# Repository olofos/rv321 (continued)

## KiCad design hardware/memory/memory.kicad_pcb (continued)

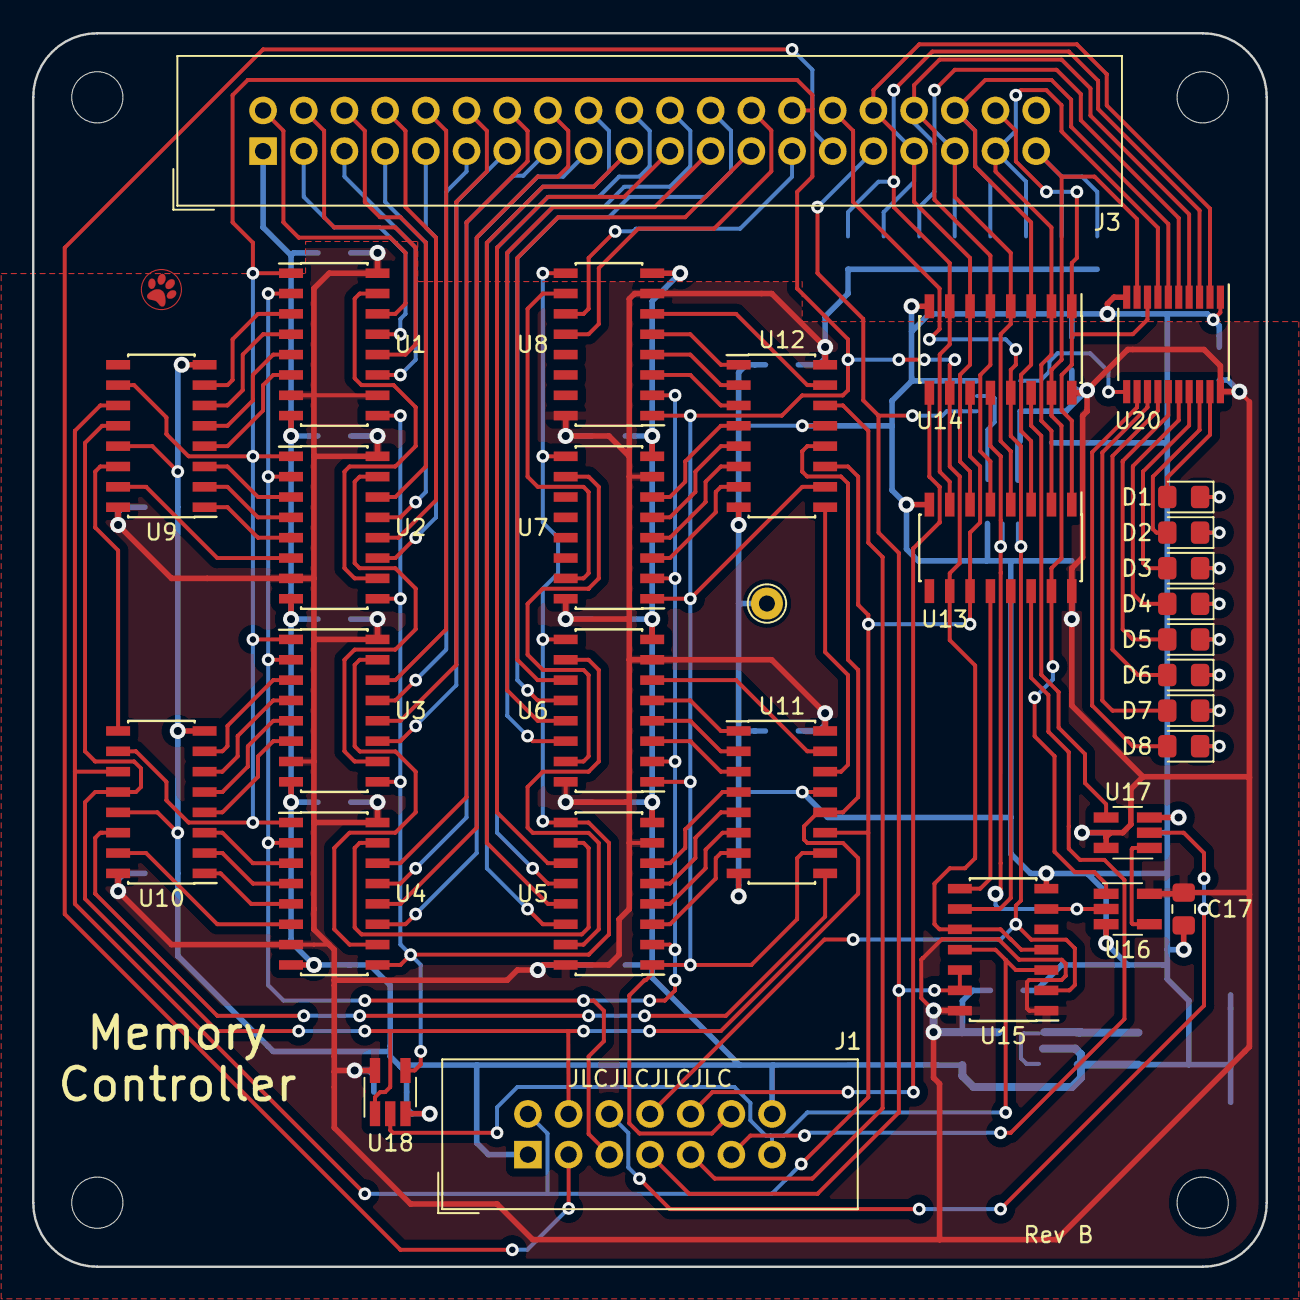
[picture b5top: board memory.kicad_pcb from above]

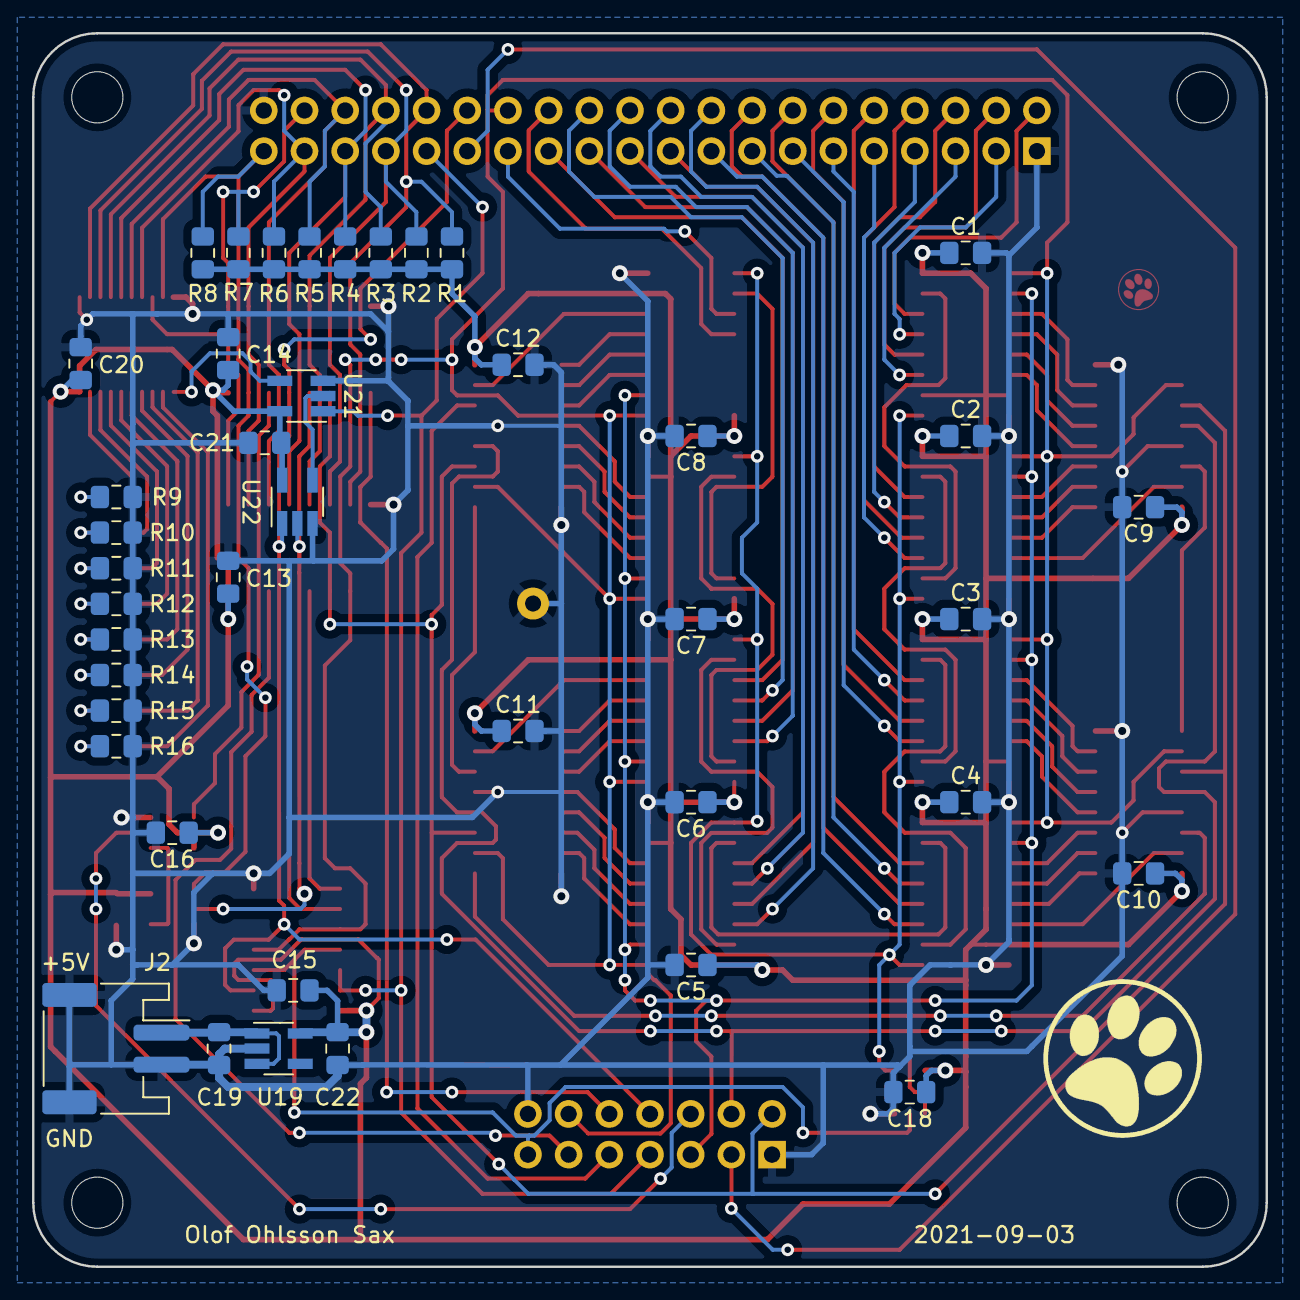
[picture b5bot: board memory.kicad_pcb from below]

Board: 2 copper layers, 77.0 x 77.0 mm, 76 parts (41 on the bottom side), 115 nets.

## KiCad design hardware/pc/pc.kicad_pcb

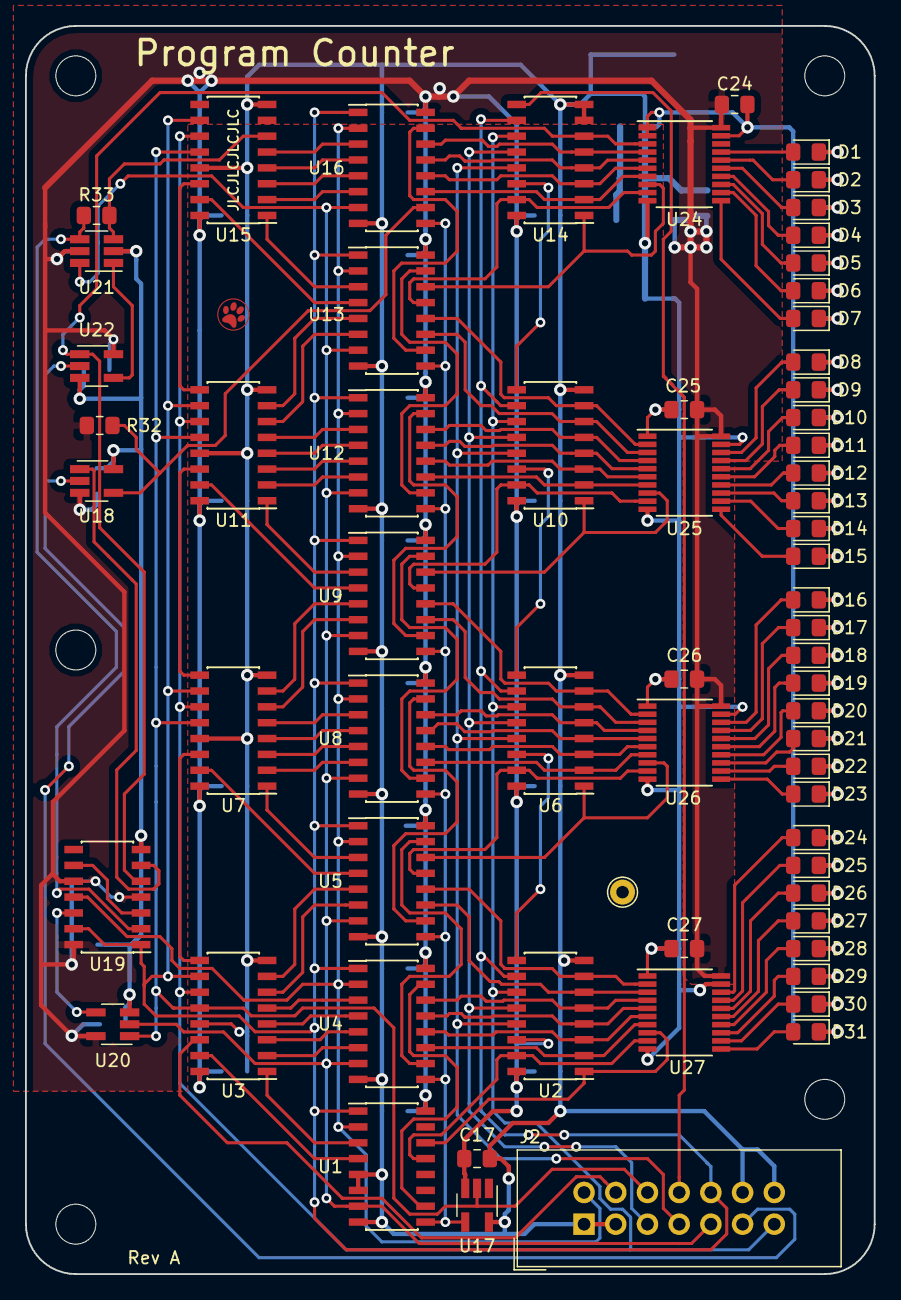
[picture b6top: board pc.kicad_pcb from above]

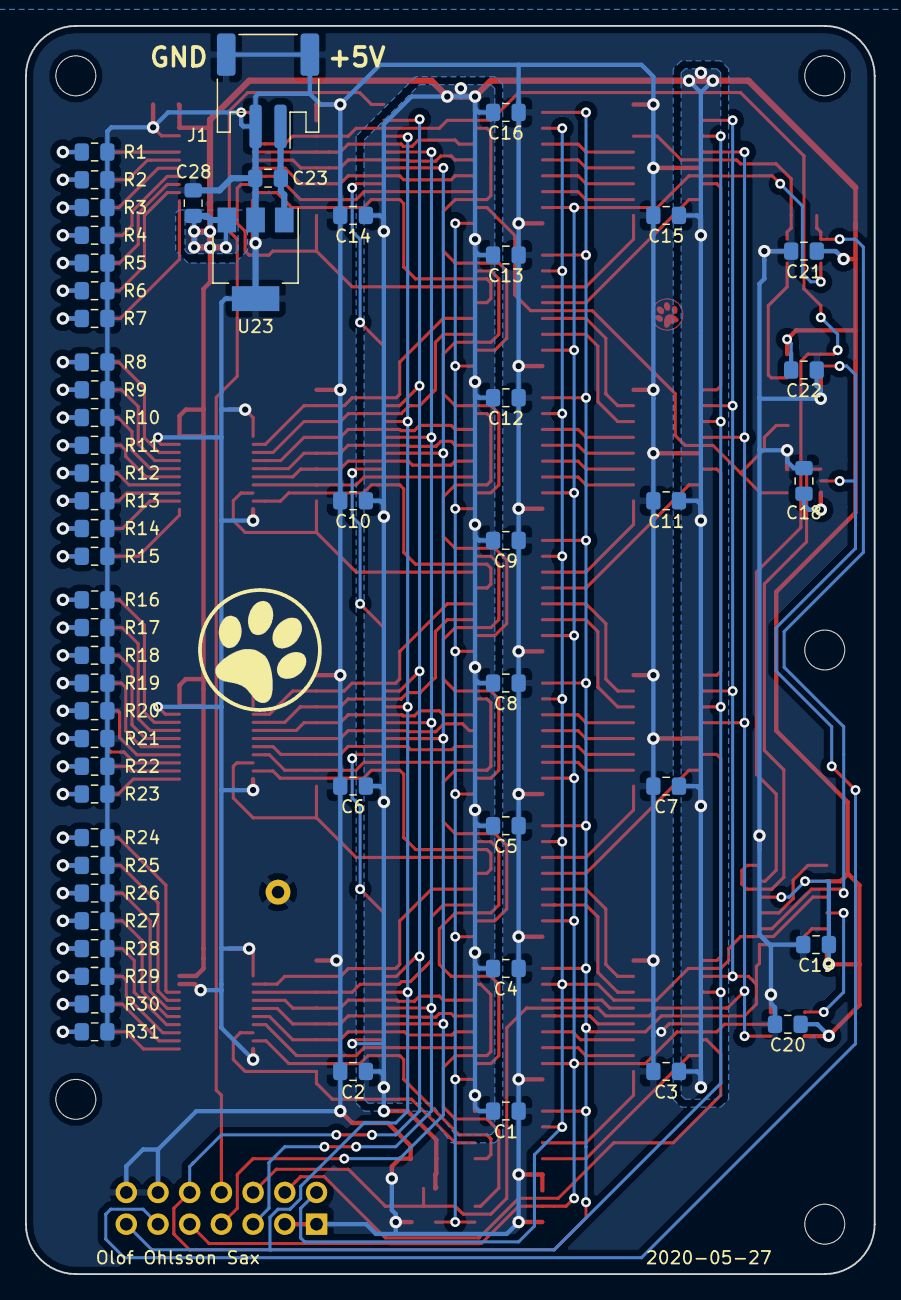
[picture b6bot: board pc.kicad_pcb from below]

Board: 2 copper layers, 68.0 x 100.0 mm, 127 parts (56 on the bottom side), 157 nets.

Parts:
C1, C2, C3, C4, C5, C6, C7, C8, C9, C10, C11, C12, C13, C14, C15, C16, C17, C18, C19, C20, C21, C22, C24, C25, C26, C27: 100n; C_0805_2012Metric_Pad1.15x1.40mm_HandSolder
C23: 4u7; C_0805_2012Metric_Pad1.15x1.40mm_HandSolder
C28: 1u; C_0805_2012Metric_Pad1.15x1.40mm_HandSolder
D1, D2, D3, D4, D5, D6, D7, D8, D9, D10, D11, D12, D13, D14, D15, D16, D17, D18, D19, D20, D21, D22, D23, D24, D25, D26, D27, D28, D29, D30, D31: LED; LED_0805_2012Metric_Pad1.15x1.40mm_HandSolder
H1, H2, H3, H5, H6: MountingHole; MountingHole_3.2mm_M3
J1: Conn_Power; JST_PH_S2B-PH-SM4-TB_1x02-1MP_P2.00mm_Horizontal
J2: Conn_PC; IDC-Header_2x07_P2.54mm_Vertical
R1, R2, R3, R4, R5, R6, R7, R8, R9, R10, R11, R12, R13, R14, R15, R16, R17, R18, R19, R20, R21, R22, R23, R24, R25, R26, R27, R28, R29, R30, R31: 330; R_0805_2012Metric_Pad1.15x1.40mm_HandSolder
R32, R33: 0; R_0805_2012Metric_Pad1.15x1.40mm_HandSolder
TP1: TestPoint; TestPoint_THTPad_D2.0mm_Drill1.0mm
U1, U4, U5, U8, U9, U12, U13, U16: 74HC161; SOIC-16_3.9x9.9mm_P1.27mm
U2, U6, U10, U14: 74HC597; SOIC-16_3.9x9.9mm_P1.27mm
U3, U7, U11, U15: 74HC595; SOIC-16_3.9x9.9mm_P1.27mm
U17: 74LVC1G04; SOT-23-5_HandSoldering
U18: 74LVC1G38; SOT-23-5_HandSoldering
U19: 74HC74; SOIC-14_3.9x8.7mm_P1.27mm
U20: 74LVC1G32; SOT-23-5_HandSoldering
U21: 74LVC1G157; SOT-23-6_Handsoldering
U22: 74LVC1G86; SOT-23-5_HandSoldering
U23: MCP1825S; SOT-223-3_TabPin2
U24, U25, U26, U27: 74HC541; TSSOP-20_4.4x6.5mm_P0.65mm

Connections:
/BUS_CLK: J2.13, U2.11, U3.11, U6.11, U7.11, U10.11, U11.11, U14.11, U15.11
/CLK: J2.2, U1.2, U4.2, U5.2, U8.2, U9.2, U12.2, U13.2, U16.2, U19.11
/CNT_2: J2.11, U18.2, U22.2
/CNT_EN: J2.9, U1.7, U4.7, U5.7, U8.7, U9.7, U12.7, U13.7, U16.7, U20.2, U21.6
/CNT_~PE: U1.9, U4.9, U5.9, U8.9, U9.9, U12.9, U13.9, U16.9, U17.4
/D1: R33.2, U15.6, U21.3
/D2: U15.5, U16.3
/D3: U15.4, U16.4
/D4: U15.3, U16.5
/D5: U15.2, U16.6
/D6: U13.3, U15.1
/D7: U13.4, U15.15
/D8: U11.7, U13.5
/D8': U11.9, U15.14
/D9: U11.6, U13.6
/D10: U11.5, U12.3
/D11: U11.4, U12.4
/D12: U11.3, U12.5
/D13: U11.2, U12.6
/D14: U9.3, U11.1
/D15: U9.4, U11.15
/D16: U7.7, U9.5
/D16': U7.9, U11.14
/D17: U7.6, U9.6
/D18: U7.5, U8.3
/D19: U7.4, U8.4
/D20: U7.3, U8.5
/D21: U7.2, U8.6
/D22: U5.3, U7.1
/D23: U5.4, U7.15
/D24: U3.7, U5.5
/D24': U3.9, U7.14
/D25: U3.6, U5.6
/D26: U3.5, U4.3
/D27: U3.4, U4.4
/D28: U3.3, U4.5
/D29: U3.2, U4.6
/D30: U1.3, U3.1
/D31: U1.4, U3.15
/IN: J2.4, U3.14
/IN_LATCH: J2.6, U3.12, U7.12, U11.12, U15.12, U17.2, U20.1
/OUT: J2.8, U14.9
/OUT_LATCH: J2.5, U2.12, U6.12, U10.12, U14.12
/OUT_S~P: J2.7, U2.13, U6.13, U10.13, U14.13
/Q1: U14.6, U19.5, U22.1, U24.3
/Q1_CLK: U19.12, U20.4
/Q1_FF_C: U19.3, U19.9
/Q1_FF_D: R33.1, U19.2, U21.4
/Q1_OR_~Q1: U21.1, U22.4
/Q2: U14.5, U16.14, U24.4
/Q3: U14.4, U16.13, U24.5
/Q4: U14.3, U16.12, U24.6
/Q5: U14.2, U16.11, U24.7
/Q6: U13.14, U14.1, U24.8
/Q7: U13.13, U14.15, U24.9
/Q8: U10.7, U13.12, U25.2
/Q8': U10.9, U14.14
/Q9: U10.6, U13.11, U25.3
/Q10: U10.5, U12.14, U25.4
/Q11: U10.4, U12.13, U25.5
/Q12: U10.3, U12.12, U25.6
/Q13: U10.2, U12.11, U25.7
/Q14: U9.14, U10.1, U25.8
/Q15: U9.13, U10.15, U25.9
/Q16: U6.7, U9.12, U26.2
/Q16': U6.9, U10.14
/Q17: U6.6, U9.11, U26.3
/Q18: U6.5, U8.14, U26.4
/Q19: U6.4, U8.13, U26.5
/Q20: U6.3, U8.12, U26.6
/Q21: U6.2, U8.11, U26.7
/Q22: U5.14, U6.1, U26.8
/Q23: U5.13, U6.15, U26.9
/Q24: U2.7, U5.12, U27.2
/Q24': U2.9, U6.14
/Q25: U2.6, U5.11, U27.3
/Q26: U2.5, U4.14, U27.4
/Q27: U2.4, U4.13, U27.5
/Q28: U2.3, U4.12, U27.6
/Q29: U2.2, U4.11, U27.7
/Q30: U1.14, U2.1, U27.8
/Q31: U1.13, U2.15, U27.9
/TC1: R32.2, U16.10, U18.4
/TC5: U13.10, U16.15
/TC9: U12.10, U13.15
/TC13: U9.10, U12.15
/TC17: U8.10, U9.15
/TC21: U5.10, U8.15
/TC25: U4.10, U5.15
/TC29: U1.10, U4.15
/V_IN: C23.1, J1.1, U23.1
/~Q1: U18.1, U19.6
/~RESET: J2.10, U1.1, U2.10, U3.10, U4.1, U5.1, U6.10, U7.10, U8.1, U9.1, U10.10, U11.10, U12.1, U13.1, U14.10, U15.10, U16.1, U19.1, U19.13
GND: C1.2, C2.2, C3.2, C4.2, C5.2, C6.2, C7.2, C8.2, C9.2, C10.2, C11.2, C12.2, C13.2, C14.2, C15.2, C16.2, C17.2, C18.2, C19.2, C20.2, C21.2, C22.2, C23.2, C24.2, C25.2, C26.2, C27.2, C28.2, J1.2, J1.MP, J2.1, J2.3, J2.12, J2.14, R1.2, R2.2, R3.2, R4.2, R5.2, R6.2, R7.2, R8.2, R9.2, R10.2, R11.2, R12.2, R13.2, R14.2, R15.2, R16.2, R17.2, R18.2, R19.2, R20.2, R21.2, R22.2, R23.2, R24.2, R25.2, R26.2, R27.2, R28.2, R29.2, R30.2, R31.2, TP1.1, U1.5, U1.6, U1.8, U2.8, U3.8, U3.13, U4.8, U5.8, U6.8, U7.8, U7.13, U8.8, U9.8, U10.8, U11.8, U11.13, U12.8, U13.8, U14.7, U14.8, U15.8, U15.13, U16.8, U17.5, U18.5, U19.7, U20.3, U21.2, U22.3, U23.2, U24.1, U24.2, U24.10, U24.19, U25.1, U25.10, U25.19, U26.1, U26.10, U26.19, U27.1, U27.10, U27.19
unnamed: D1.1, R1.1
unnamed: D1.2, U24.17
unnamed: D2.1, R2.1
unnamed: D2.2, U24.16
unnamed: D3.1, R3.1
unnamed: D3.2, U24.15
unnamed: D4.1, R4.1
unnamed: D4.2, U24.14
unnamed: D5.1, R5.1
unnamed: D5.2, U24.13
unnamed: D6.1, R6.1
unnamed: D6.2, U24.12
unnamed: D7.1, R7.1
unnamed: D7.2, U24.11
unnamed: D8.1, R8.1
unnamed: D8.2, U25.18
unnamed: D9.1, R9.1
unnamed: D9.2, U25.17
unnamed: D10.1, R10.1
unnamed: D10.2, U25.16
unnamed: D11.1, R11.1
unnamed: D11.2, U25.15
unnamed: D12.1, R12.1
unnamed: D12.2, U25.14
unnamed: D13.1, R13.1
unnamed: D13.2, U25.13
unnamed: D14.1, R14.1
unnamed: D14.2, U25.12
unnamed: D15.1, R15.1
unnamed: D15.2, U25.11
unnamed: D16.1, R16.1
unnamed: D16.2, U26.18
unnamed: D17.1, R17.1
unnamed: D17.2, U26.17
unnamed: D18.1, R18.1
unnamed: D18.2, U26.16
unnamed: D19.1, R19.1
unnamed: D19.2, U26.15
unnamed: D20.1, R20.1
unnamed: D20.2, U26.14
unnamed: D21.1, R21.1
unnamed: D21.2, U26.13
unnamed: D22.1, R22.1
unnamed: D22.2, U26.12
unnamed: D23.1, R23.1
unnamed: D23.2, U26.11
unnamed: D24.1, R24.1
unnamed: D24.2, U27.18
unnamed: D25.1, R25.1
unnamed: D25.2, U27.17
unnamed: D26.1, R26.1
unnamed: D26.2, U27.16
unnamed: D27.1, R27.1
unnamed: D27.2, U27.15
unnamed: D28.1, R28.1
unnamed: D28.2, U27.14
unnamed: D29.1, R29.1
unnamed: D29.2, U27.13
unnamed: D30.1, R30.1
unnamed: D30.2, U27.12
unnamed: D31.1, R31.1
unnamed: D31.2, U27.11
VCC: C1.1, C2.1, C3.1, C4.1, C5.1, C6.1, C7.1, C8.1, C9.1, C10.1, C11.1, C12.1, C13.1, C14.1, C15.1, C16.1, C17.1, C18.1, C19.1, C20.1, C21.1, C22.1, C24.1, C25.1, C26.1, C27.1, C28.1, R32.1, U1.16, U2.14, U2.16, U3.16, U4.16, U5.16, U6.16, U7.16, U8.16, U9.16, U10.16, U11.16, U12.16, U13.16, U14.16, U15.16, U16.16, U17.3, U18.3, U19.4, U19.10, U19.14, U20.5, U21.5, U22.5, U23.3, U24.20, U25.20, U26.20, U27.20

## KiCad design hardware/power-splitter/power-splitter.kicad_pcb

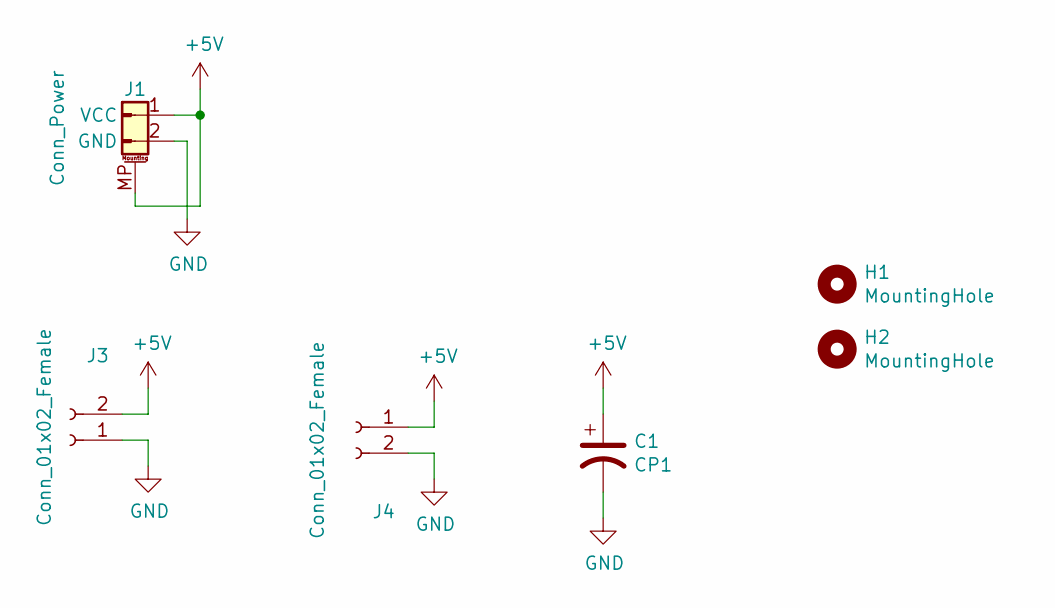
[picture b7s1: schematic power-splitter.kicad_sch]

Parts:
C1: CP1; CP_Elec_5x5.3
H1, H2: MountingHole; MountingHole_3.2mm_M3
J1: Conn_Power; JST_PH_S2B-PH-SM4-TB_1x02-1MP_P2.00mm_Horizontal
J3, J4: Conn_01x02_Female; TerminalBlock_01x02_p5.08

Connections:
+5V: C1.1, J1.1 (VCC), J1.MP, J3.2, J4.1
GND: C1.2, J1.2 (GND), J3.1, J4.2

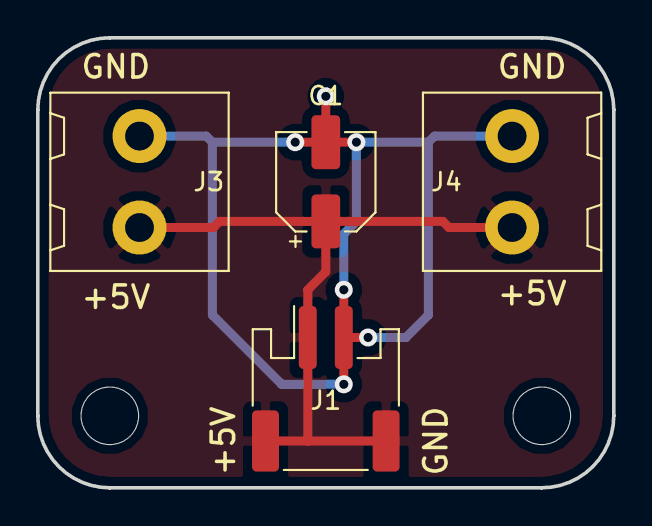
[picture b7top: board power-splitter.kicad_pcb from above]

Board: 2 copper layers, 32.0 x 25.0 mm, 6 parts (0 on the bottom side), 2 nets.

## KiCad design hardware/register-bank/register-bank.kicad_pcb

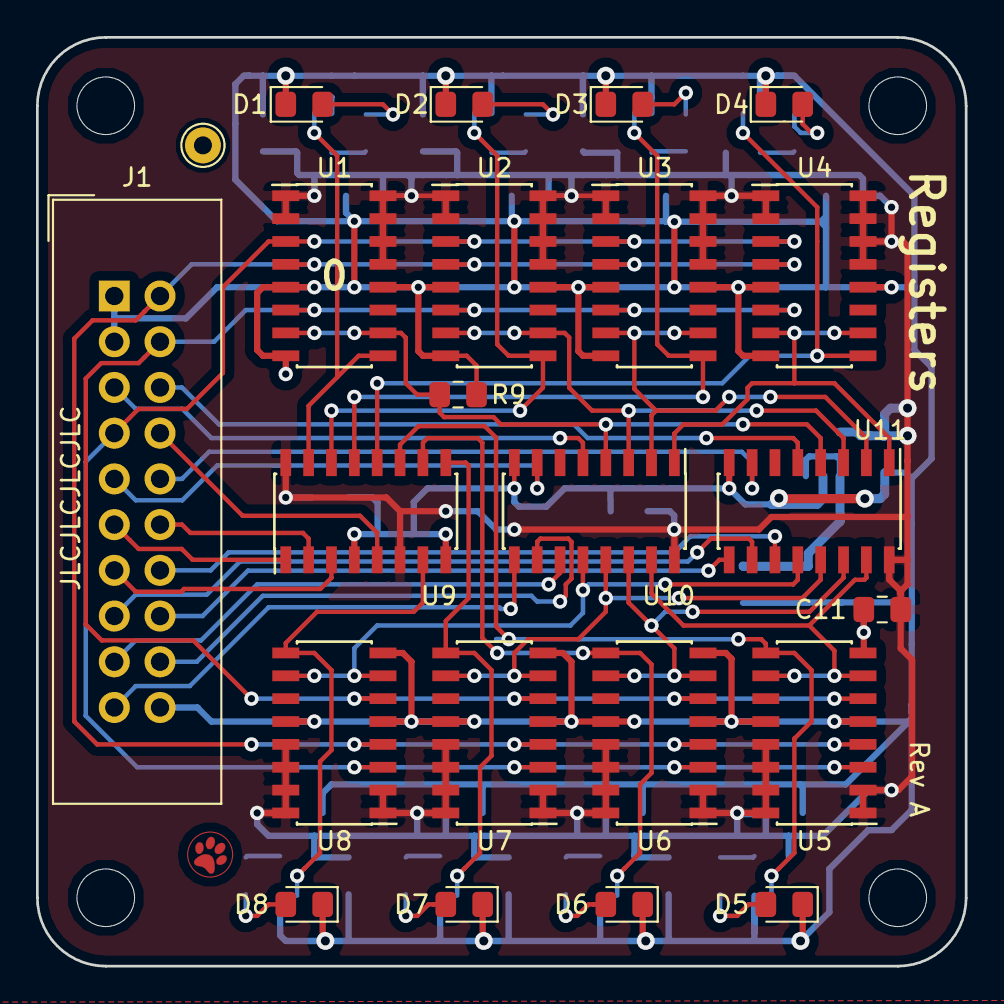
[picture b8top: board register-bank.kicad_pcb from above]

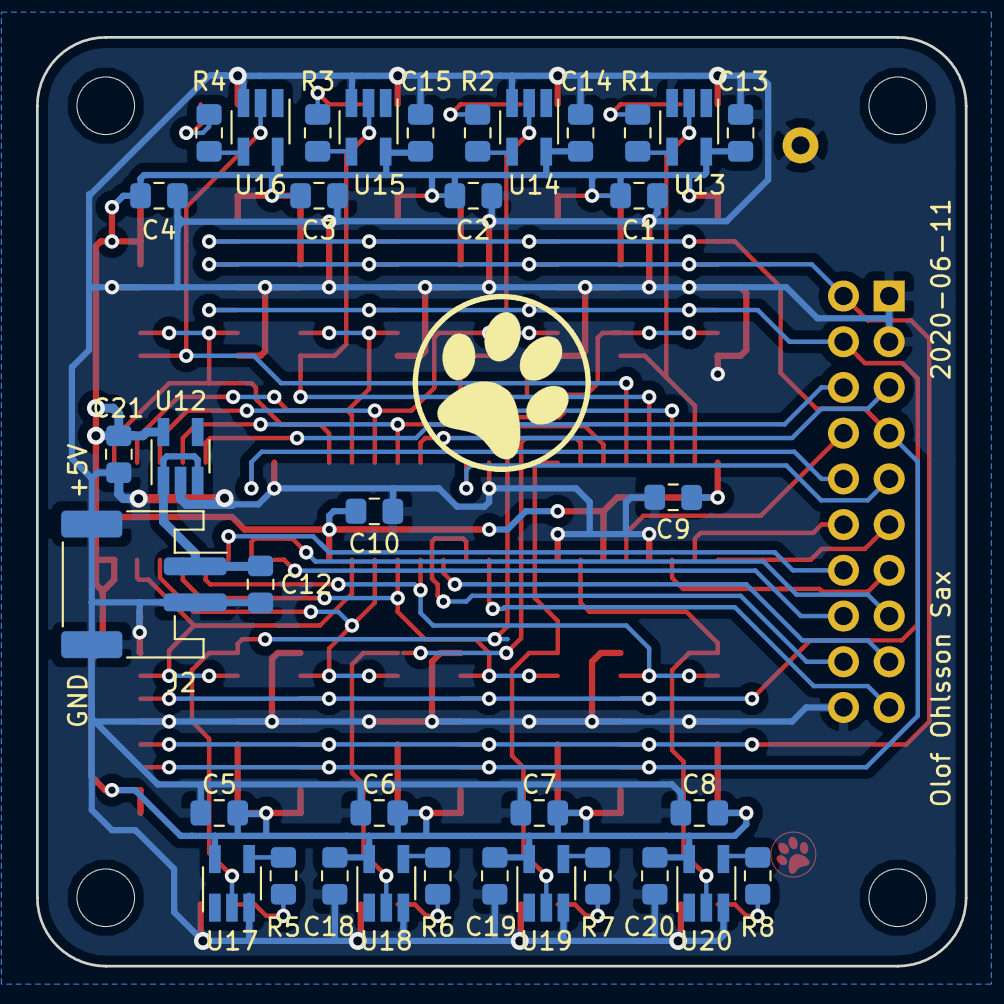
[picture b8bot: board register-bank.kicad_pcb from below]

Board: 2 copper layers, 51.6 x 51.6 mm, 63 parts (36 on the bottom side), 52 nets.

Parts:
C1, C2, C3, C4, C5, C6, C7, C8, C9, C10, C11, C13, C14, C15, C18, C19, C20: 100n; C_0805_2012Metric_Pad1.15x1.40mm_HandSolder
C12, C21: 1u; C_0805_2012Metric_Pad1.15x1.40mm_HandSolder
D1, D2, D3, D4, D5, D6, D7, D8: LED; LED_0805_2012Metric_Pad1.15x1.40mm_HandSolder
H1, H2, H3, H4: MountingHole; MountingHole_3.2mm_M3
J1: Conn_Reg; IDC-Header_2x10_P2.54mm_Vertical
J2: Conn_Power; JST_PH_S2B-PH-SM4-TB_1x02-1MP_P2.00mm_Horizontal
R1, R2, R3, R4, R5, R6, R7, R8: 330; R_0805_2012Metric_Pad1.15x1.40mm_HandSolder
R9: 0; R_0805_2012Metric_Pad1.15x1.40mm_HandSolder
TP1: TestPoint; TestPoint_THTPad_D2.0mm_Drill1.0mm
U1, U2, U3, U4, U5, U6, U7, U8: HEF4557B; SOIC-16_3.9x9.9mm_P1.27mm
U9: 74HC138; SOIC-16_3.9x9.9mm_P1.27mm
U10, U11: 74HC251; SOIC-16_3.9x9.9mm_P1.27mm
U12: MIC5504-3.3YM5; SOT-23-5_HandSoldering
U13, U14, U15, U16, U17, U18, U19, U20: 74LVC1G04; SOT-23-5_HandSoldering

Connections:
/BUS_CLK: J1.2, U1.4, U2.4, U3.4, U4.4, U5.4, U6.4, U7.4, U8.4
/RAOUT: J1.5, U10.5
/RAS0: J1.17, U10.11
/RAS1: J1.18, U10.10
/RAS2: J1.19, U10.9
/RBOUT: J1.6, U11.5
/RBS0: J1.14, U11.11
/RBS1: J1.15, U11.10
/RBS2: J1.16, U11.9
/RESET: J1.7, U1.3, U2.3, U3.3, U4.3, U5.3, U6.3, U7.3, U8.3
/RIN: J1.4, U1.6, U2.6, U3.6, U4.6, U5.6, U6.6, U7.6, U8.6
/RINS0: J1.11, U9.1
/RINS1: J1.12, U9.2
/RINS2: J1.13, U9.3
/ROUT0: R9.1, U1.7, U1.10, U10.4, U11.4
/ROUT1: U2.7, U2.10, U10.3, U11.3
/ROUT2: U3.7, U3.10, U10.2, U11.2
/ROUT3: U4.7, U4.10, U10.1, U11.1
/ROUT4: U5.7, U5.10, U10.15, U11.15
/ROUT5: U6.7, U6.10, U10.14, U11.14
/ROUT6: U7.7, U7.10, U10.13, U11.13
/ROUT7: U8.7, U8.10, U10.12, U11.12
/V_IN: C12.1, J2.1, U12.1, U12.3
/~RIN_EN0: U1.9, U9.15, U13.2
/~RIN_EN1: U2.9, U9.14, U14.2
/~RIN_EN2: U3.9, U9.13, U15.2
/~RIN_EN3: U4.9, U9.12, U16.2
/~RIN_EN4: U5.9, U9.11, U17.2
/~RIN_EN5: U6.9, U9.10, U18.2
/~RIN_EN6: U7.9, U9.9, U19.2
/~RIN_EN7: U8.9, U9.7, U20.2
/~RIN_EN: J1.8, U9.5
/~ROUT_EN_A: J1.9, U10.7
/~ROUT_EN_B: J1.10, U11.7
GND: C1.2, C2.2, C3.2, C4.2, C5.2, C6.2, C7.2, C8.2, C9.2, C10.2, C11.2, C12.2, C13.2, C14.2, C15.2, C18.2, C19.2, C20.2, C21.2, D1.1, D2.1, D3.1, D4.1, D5.1, D6.1, D7.1, D8.1, J1.1, J1.3, J1.20, J2.2, J2.MP, R9.2, TP1.1, U1.5, U1.8, U1.12, U2.5, U2.8, U2.12, U3.5, U3.8, U3.12, U4.5, U4.8, U4.12, U5.5, U5.8, U5.12, U6.5, U6.8, U6.12, U7.5, U7.8, U7.12, U8.5, U8.8, U8.12, U9.4, U9.8, U10.8, U11.8, U12.2, U13.3, U14.3, U15.3, U16.3, U17.3, U18.3, U19.3, U20.3
unnamed: D1.2, R1.1
unnamed: D2.2, R2.1
unnamed: D3.2, R3.1
unnamed: D4.2, R4.1
unnamed: D5.2, R5.1
unnamed: D6.2, R6.1
unnamed: D7.2, R7.1
unnamed: D8.2, R8.1
unnamed: R1.2, U13.4
unnamed: R2.2, U14.4
unnamed: R3.2, U15.4
unnamed: R4.2, U16.4
unnamed: R5.2, U17.4
unnamed: R6.2, U18.4
unnamed: R7.2, U19.4
unnamed: R8.2, U20.4
VCC: C1.1, C2.1, C3.1, C4.1, C5.1, C6.1, C7.1, C8.1, C9.1, C10.1, C11.1, C13.1, C14.1, C15.1, C18.1, C19.1, C20.1, C21.1, U1.1, U1.2, U1.13, U1.14, U1.15, U1.16, U2.1, U2.2, U2.13, U2.14, U2.15, U2.16, U3.1, U3.2, U3.13, U3.14, U3.15, U3.16, U4.1, U4.2, U4.13, U4.14, U4.15, U4.16, U5.1, U5.2, U5.13, U5.14, U5.15, U5.16, U6.1, U6.2, U6.13, U6.14, U6.15, U6.16, U7.1, U7.2, U7.13, U7.14, U7.15, U7.16, U8.1, U8.2, U8.13, U8.14, U8.15, U8.16, U9.6, U9.16, U10.16, U11.16, U12.5, U13.5, U14.5, U15.5, U16.5, U17.5, U18.5, U19.5, U20.5
